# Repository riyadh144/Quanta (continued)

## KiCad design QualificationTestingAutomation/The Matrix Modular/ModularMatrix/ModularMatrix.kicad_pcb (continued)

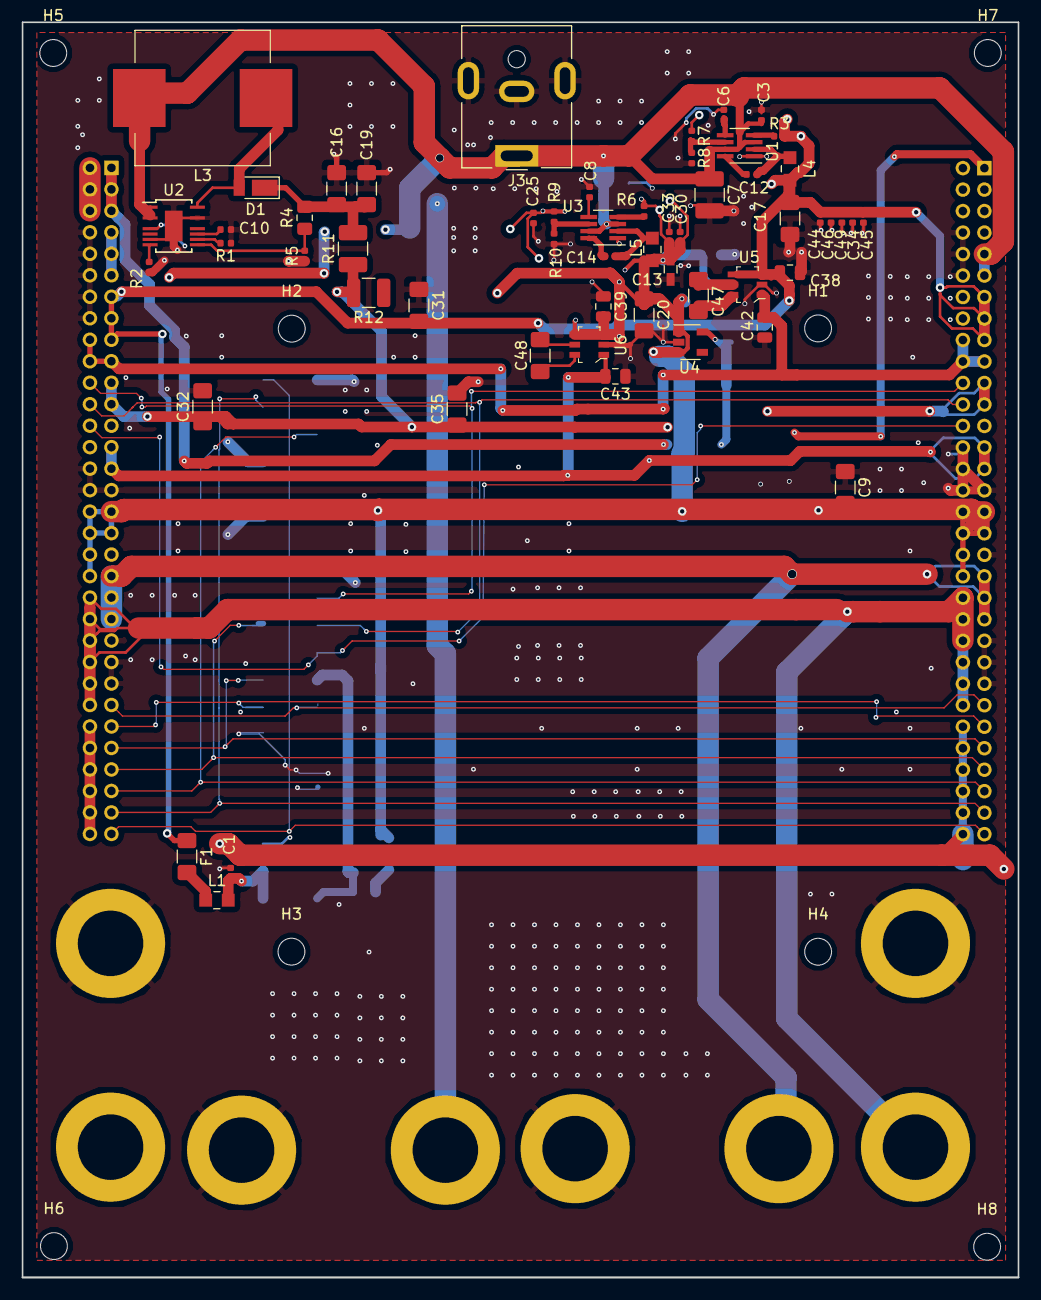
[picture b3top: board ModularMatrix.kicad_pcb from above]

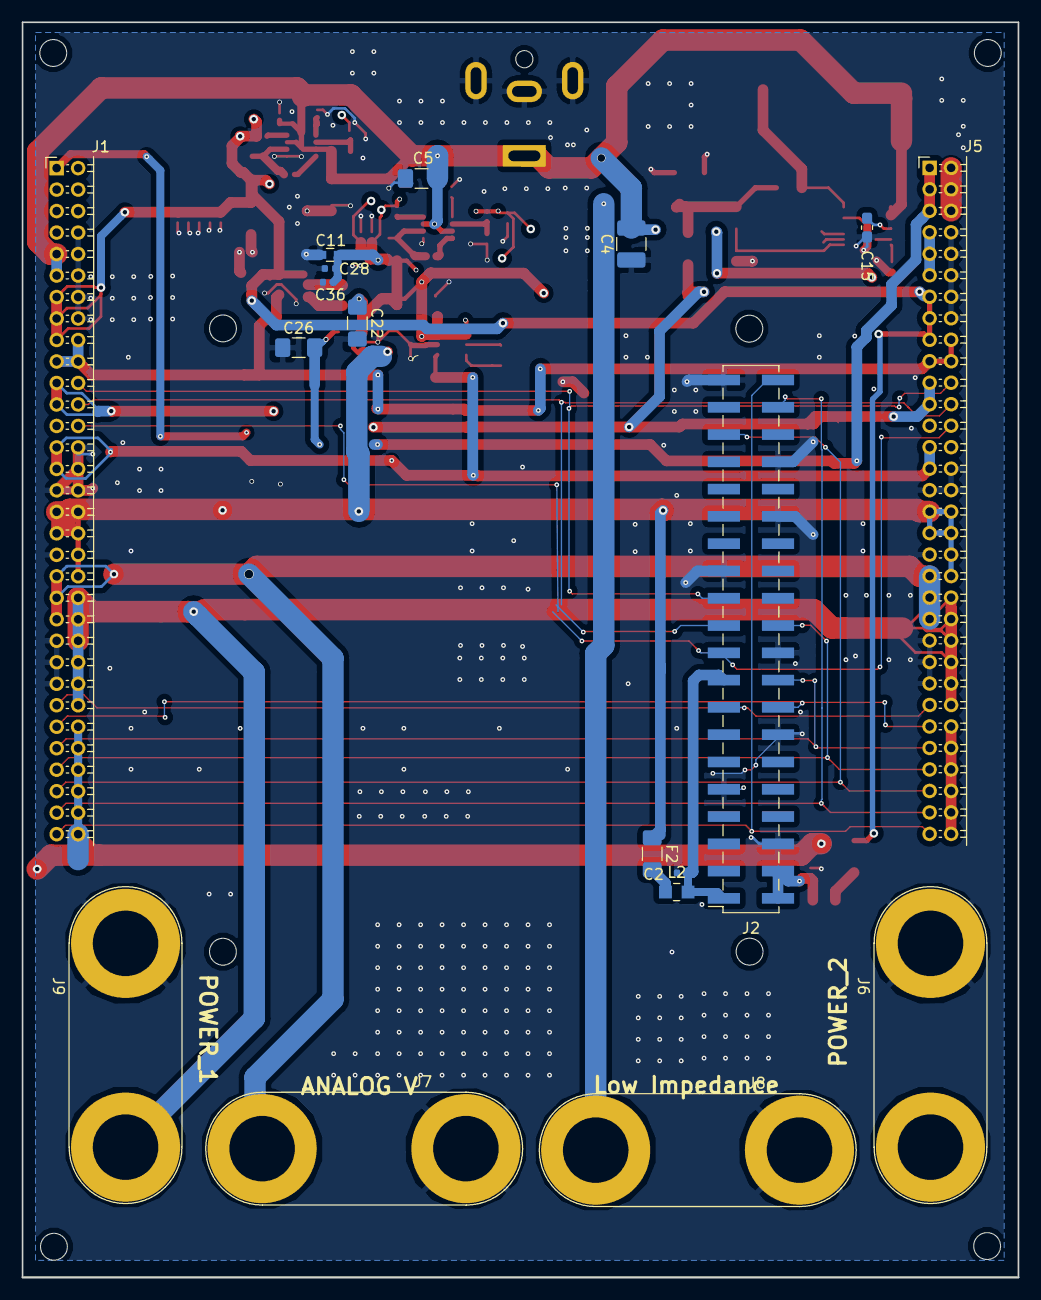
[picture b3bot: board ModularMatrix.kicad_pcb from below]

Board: 4 copper layers, 92.7 x 116.8 mm, 82 parts (18 on the bottom side), 47 nets.

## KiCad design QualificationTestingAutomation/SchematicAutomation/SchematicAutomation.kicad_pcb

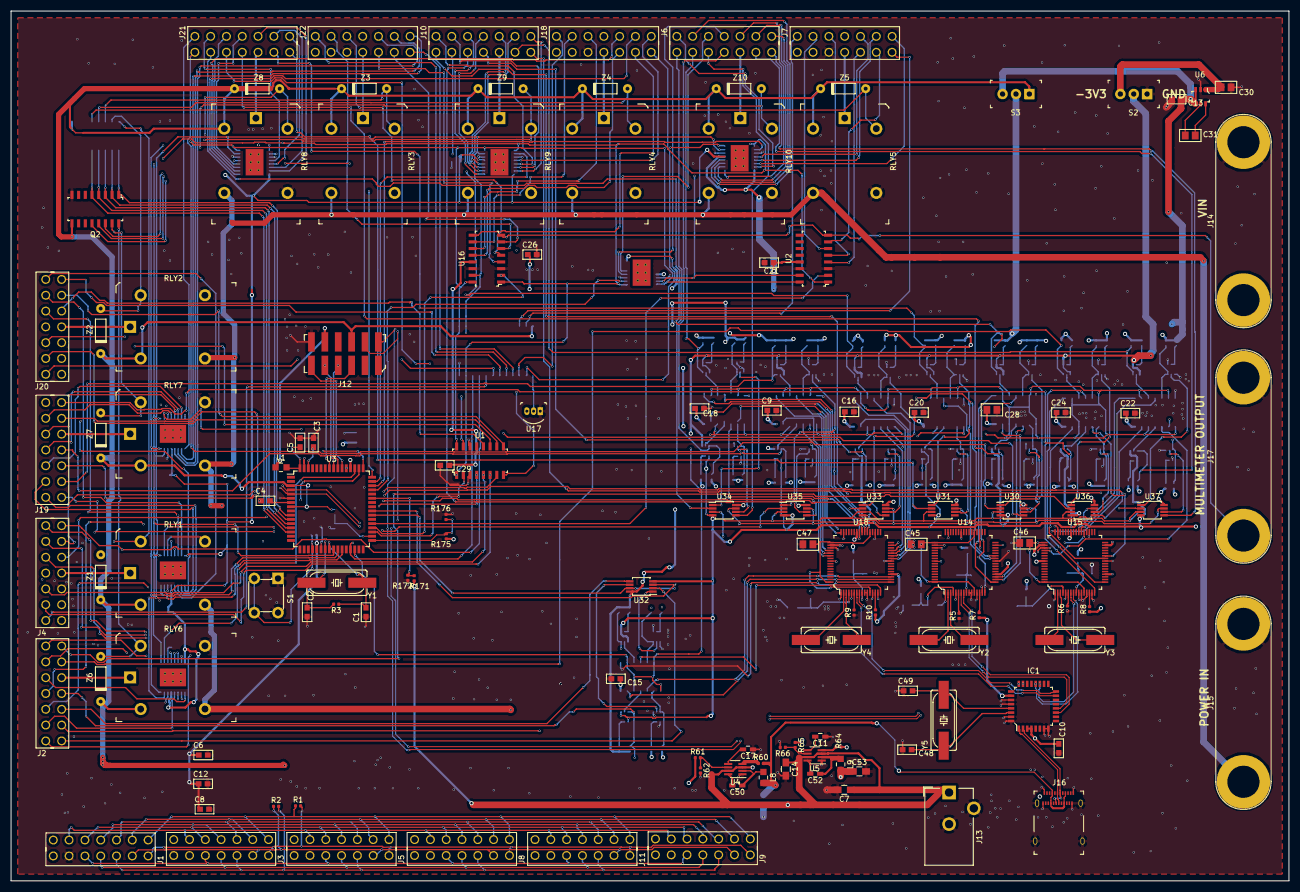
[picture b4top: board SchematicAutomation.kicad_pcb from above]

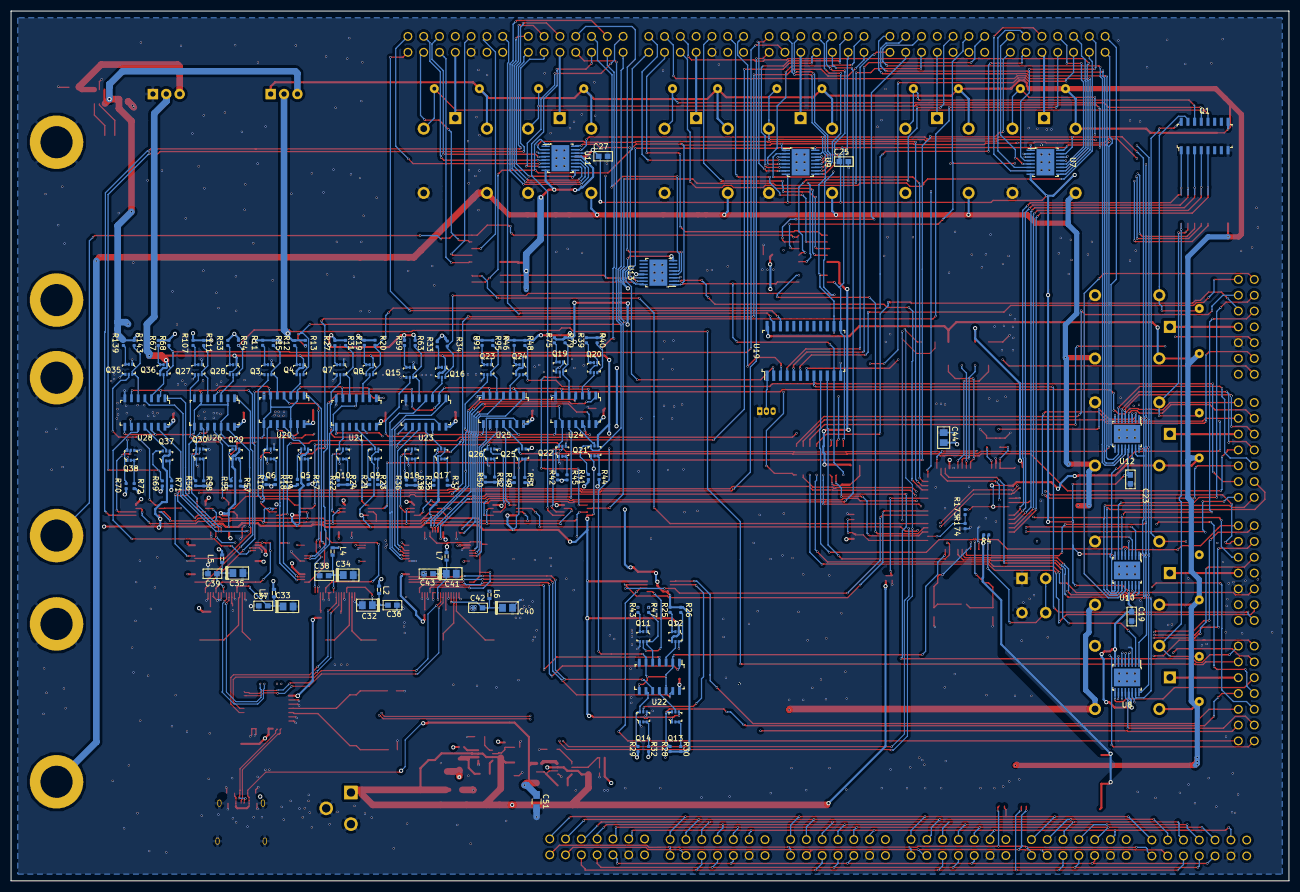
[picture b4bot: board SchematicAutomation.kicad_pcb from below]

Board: 4 copper layers, 242.6 x 165.1 mm, 268 parts (140 on the bottom side), 343 nets.

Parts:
C1, C2, C48, C49: 20pF; C-0603
C3, C5, C36, C37, C38, C39, C42, C43: 100nF; C-0603
C4: 1uF; C-0603
C6, C8, C9, C10, C12, C13, C15, C16, C18, C19, C20, C21, C22, C23, C24, C25, C26, C27, C29: .01uF; C-0603
C7, C14: 22uF; C_0805_HandSoldering
C11, C17: 8.2nF; C_0603_HandSoldering
C28, C30: 2.2uF; C-0805
C31: 1uF; C-0805
C32, C33, C34, C35, C40, C41: 4.7uF; CPL-0805
C44: 4.7uF; C-0805
C45, C46, C47: 3.3uF; C-0805
C50, C52: 100nF; C_0603_HandSoldering
C51, C53: 47uF; C_0805_HandSoldering
IC1: TUSB2046B; LQFP-32_7x7mm
J1, J2, J3, J4, J5, J6, J7, J8, J9, J10, J11, J18, J19, J20, J21, J22: OBD Connector; 3MM
J12: 0015912120; PinHeader_2x6_P2.54mm_Vertical_SMD
J13: Barrel_Jack_MountingPin; Barrel_Jack_CUI_PJ-102AH
J14, J15, J17: Banana Jack; Banana_Jack_2Pin
J16: 12401610E4_2A; USB_Type_C_Female__12401610E4_2A
L1: 10uH; 0805
L2, L3, L4, L5, L6, L7: L_Core_Ferrite; 0603
L8, L9: 3.3uH; 0805
Q1, Q2: ULN2003ADR; SOIC-16_W3.90mm
Q3, Q4, Q5, Q6, Q7, Q8, Q9, Q10, Q11, Q12, Q13, Q14, Q15, Q16, Q17, Q18, Q19, Q20, Q21, Q22, Q23, Q24, Q25, Q26, Q27, Q28, Q29, Q30, Q35, Q36, Q37, Q38: 2N7002DW; SOT-363
R1, R2: R120; R_0402_1005Metric
R3: 1M; R_0402_1005Metric
R4, R60, R64, R171, R173, R175, R176: 100K; R_0402_1005Metric
R5, R6, R9: 12K; R_0402_1005Metric
R7, R8, R10: 1K; R_0402_1005Metric
R11, R12, R13, R14, R15, R16, R17, R18, R19, R20, R21, R22, R23, R24, R25, R26, R27, R28, R29, R30, R31, R32, R33, R34, R35, R36, R37, R38, R39, R40, R41, R42, R43, R44, R45, R46, R47, R48, R49, R50, R51, R52, R53, R54, R55, R56, R57, R58, R59, R63, R67, R68, R69, R70, R71, R72, R75, R79, R91, R95, R107, R111, R139, R143: 10k; R_0402_1005Metric
R61: 56.2K; R_0402_1005Metric
R62, R66, R172: 10K; R_0402_1005Metric
R65: 33.2K; R_0402_1005Metric
R174: 50K; R_0402_1005Metric
RLY1, RLY2, RLY3, RLY4, RLY5, RLY6, RLY7, RLY8, RLY9, RLY10: G5LE-14_DC5; Relay_THT_G5LE-14
S1: 1825910-6; Switch_Tactile_THT_6x6mm
S2, S3: ATE1D-2M3-10-Z; Switch_Toggle_ATE1D-2M3-10-Z
U1, U2, U16: DG408LE; SOIC-16_W3.90mm
U3: AT90USB1287-AU; TQFP-64_14x14mm_P0.8mm
U4, U5: TPS563210; SOT-23-8_Handsoldering
U6: LM2776; SOT-23-6
U7, U8, U9, U10, U11, U12, U13: MAX14752; TSSOP-16-1EP_W4.40mm
U14, U15, U18: FT4232HL-REEL; LQFP-64_10x10mm
U17: DS18B20_; TO-92-3
U19: CD74HC4067SM96; SSOP-24_W5.30mm
U20, U21, U22, U23, U24, U25, U26, U28: CD4070B; SOIC-14_W3.9mm
U30, U31, U32, U33, U34, U35, U36, U37: MAX324CUA; MSOP-8_3x3mm_Pitch0.65mm
Y1: 16MHz; HC49UP
Y2, Y3, Y4: 12MHz; HC49UP
Y5: 6MHz; HC49UP
Z1, Z2, Z3, Z4, Z5, Z6, Z7, Z8, Z9, Z10: 1N5231BTR; DO-35

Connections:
1_ADC0: J4.10, U8.4
1_ADC1: J2.14, U8.7
1_ADC2: J4.8, U8.6
1_ADC3: J4.9, U8.5
1_CANHigh: J1.1, J3.1, J5.1, J8.1, J9.1, J11.1, R1.1
1_CANLow: J1.14, J3.14, J5.14, J8.14, J9.14, J11.14, R1.2
1_CAN_MS_H: J1.13, J3.13, J5.13, J8.13, J9.13, J11.13, R2.1
1_CAN_MS_L: J1.12, J3.12, J5.12, J8.12, J9.12, J11.12, R2.2
1_CTS: J2.3, U32.5
1_GarminPWR: J2.5, RLY6.1
1_GarminRX: J2.6, Q28.6, R54.1
1_GarminTX: J2.7, U36.2
1_IN0: J2.13, U8.12
1_IN1: J2.8, U8.11
1_IN2: J2.9, U8.10
1_IN3: J2.10, U8.9
1_IN4: J2.11, U10.4
1_IN5: J2.12, U10.5
1_ISO-K: J1.10, J3.10, J5.10, J8.10, J9.10, J11.10
1_ISO-Low: J1.4, J3.4, J5.4, J8.4, J9.4, J11.4
1_J1708-RXD: J1.2, J3.2, J5.2, J8.2, J9.2, J11.2
1_J1708-TXD: J1.3, J3.3, J5.3, J8.3, J9.3, J11.3
1_J1850+: J1.6, J3.6, J5.6, J8.6, J9.6, J11.6
1_J1850-: J1.5, J3.5, J5.5, J8.5, J9.5, J11.5
1_OUT0: J4.5, U1.4
1_OUT1: J4.12, U1.5
1_OUT2: J4.13, U1.6
1_OUT3: J4.6, U1.7
1_OWB_MAIN: J4.14, U19.8
1_OWB_SEC: J4.7, U19.9
1_REL: Q1.1, Q2.1, U3.10
1_RTS: J2.4, Q13.6, R28.1
1_RX: J2.2, Q12.6, R26.1
1_SWC_BUS: J1.11, J3.11, J5.11, J8.11, J9.11, J11.11
1_TX: J2.1, U32.2
1_Vin: J4.4, RLY1.1
2_ADC0: J20.10, U10.6
2_ADC1: J19.14, U10.11
2_ADC2: J20.8, U10.12
2_ADC3: J20.9, U10.7
2_CTS: J19.3, U35.5
2_GarminPWR: J19.5, RLY7.1
2_GarminRX: J19.6, U36.5
2_GarminTX: J19.7, Q29.6, R55.1
2_IN0: J19.13, U10.10
2_IN1: J19.8, U10.9
2_IN2: J19.9, U12.4
2_IN3: J19.10, U12.5
2_IN4: J19.11, U12.6
2_IN5: J19.12, U12.7
2_OUT0: J20.5, U1.12
2_OUT1: J20.12, U1.11
2_OUT2: J20.13, U1.10
2_OUT3: J20.6, U1.9
2_OWB_MAIN: J20.14, U19.7
2_OWB_SEC: J20.7, U19.6
2_REL: Q1.2, Q2.2, U3.11
2_RTS: J19.4, Q25.6, R49.1
2_RX: J19.2, Q24.6, R48.1
2_TX: J19.1, U35.2
2_Vin: J20.4, RLY2.1
3_ADC0: J22.10, U12.12
3_ADC1: J21.14, U12.9
3_ADC2: J22.8, U12.10
3_ADC3: J22.9, U12.11
3_CTS: J21.3, U30.5
3_GarminPWR: J21.5, RLY8.1
3_GarminRX: J21.6, Q8.6, R20.1
3_GarminTX: J21.7, U31.2
3_IN0: J21.13, U7.4
3_IN1: J21.8, U7.5
3_IN2: J21.9, U7.6
3_IN3: J21.10, U7.7
3_IN4: J21.11, U7.12
3_IN5: J21.12, U7.11
3_OUT0: J22.5, U16.4
3_OUT1: J22.12, U16.5
3_OUT2: J22.13, U16.6
3_OUT3: J22.6, U16.7
3_OWB_MAIN: J22.14, U19.5
3_OWB_SEC: J22.7, U19.4
3_REL: Q1.3, Q2.3, U3.12
3_RTS: J21.4, Q5.6, R14.1
3_RX: J21.2, Q4.6, R13.1
3_TX: J21.1, U30.2
3_Vin: J22.4, RLY3.1
4_ADC0: J18.10, U7.10
4_ADC1: J10.14, U9.5
4_ADC2: J18.8, U9.4
4_ADC3: J18.9, U7.9
4_CTS: J10.3, U33.5
4_GarminPWR: J10.5, RLY9.1
4_GarminRX: J10.6, Q36.6, R68.1
4_GarminTX: J10.7, U37.2
4_IN0: J10.13, U9.6
4_IN1: J10.8, U9.7
4_IN2: J10.9, U9.12
4_IN3: J10.10, U9.11
4_IN4: J10.11, U9.10
4_IN5: J10.12, U9.9
4_OUT0: J18.5, U16.12
4_OUT1: J18.12, U16.11
4_OUT2: J18.13, U16.10
4_OUT3: J18.6, U16.9
4_OWB_MAIN: J18.14, U19.3
4_OWB_SEC: J18.7, U19.2
4_REL: Q1.4, Q2.4, U3.13
4_RTS: J10.4, Q17.6, R35.1
4_RX: J10.2, Q16.6, R34.1
4_TX: J10.1, U33.2
4_Vin: J18.4, RLY4.1
5_ADC0: J7.10, U11.4
5_ADC1: J6.14, U11.7
5_ADC2: J7.8, U11.6
5_ADC3: J7.9, U11.5
5_CTS: J6.3, U34.5
5_GarminPWR: J6.5, RLY10.1
5_GarminRX: J6.6, Q37.6, R69.1
5_GarminTX: J6.7, U37.5
5_IN0: J6.13, U11.12
5_IN1: J6.8, U11.11
5_IN2: J6.9, U11.10
5_IN3: J6.10, U11.9
5_IN4: J6.11, U13.4
5_IN5: J6.12, U13.5
5_OUT0: J7.5, U2.4
5_OUT1: J7.12, U2.5
5_OUT2: J7.13, U2.6
5_OUT3: J7.6, U2.7
5_OWB_MAIN: J7.14, U19.23
5_OWB_SEC: J7.7, U19.22
5_REL: Q1.5, Q2.5, U3.14
5_RTS: J6.4, Q21.6, R41.1
5_RX: J6.2, Q20.6, R40.1
5_TX: J6.1, U34.2
5_Vin: J7.4, RLY5.1
+3V3: C6.1, C8.1, C9.1, C10.1, C12.1, C13.1, C15.1, C16.1, C18.1, C20.1, C22.1, C24.1, C28.2, C44.2, C53.1, IC1.3, IC1.4, IC1.26, J12.11, L1.1, L2.2, L3.2, L4.2, L5.2, L6.2, L7.2, L9.2, R4.2, R7.1, R8.1, R10.1, R11.1, R15.2, R16.2, R18.1, R22.2, R24.1, R27.1, R29.2, R31.2, R32.1, R36.2, R38.1, R42.2, R43.1, R45.1, R47.2, R50.2, R52.1, R56.2, R58.1, R59.1, R63.2, R64.2, R65.1, R70.2, R72.1, R75.1, R79.2, R91.1, R95.2, R107.1, R111.2, R139.1, R143.2, R175.1, S3.3, U3.21, U3.52, U6.3, U6.4, U14.20, U14.31, U14.42, U14.50, U14.56, U15.20, U15.31, U15.42, U15.50, U15.56, U18.20, U18.31, U18.42, U18.50, U18.56, U20.14, U21.14, U22.14, U23.14, U24.14, U25.14, U26.14, U28.14
+5V: C51.1, J12.9, J16.A4, J16.A9, J16.B4, J16.B9, L8.2, Q1.9, Q2.9, R60.2, R61.1, R173.1, RLY1.2, RLY2.2, RLY3.2, RLY4.2, RLY5.2, RLY6.2, RLY7.2, RLY8.2, RLY9.2, RLY10.2, S3.1, U3.3, U3.8, U19.24, Z1.K, Z2.K, Z3.K, Z4.K, Z5.K, Z6.K, Z7.K, Z8.K, Z9.K, Z10.K
+12V: C7.1, C14.1, J13.1, R171.1, U4.3, U4.7, U5.3, U5.7
+VSW: R12.1, R13.2, R14.2, R17.1, R19.1, R20.2, R21.2, R23.1, R25.1, R26.2, R28.2, R30.1, R33.1, R34.2, R35.2, R37.1, R39.1, R40.2, R41.2, R44.1, R46.1, R48.2, R49.2, R51.1, R53.1, R54.2, R55.2, R57.1, R67.1, R68.2, R69.2, R71.1, S3.2, U30.8, U31.8, U32.8, U33.8, U34.8, U35.8, U36.8, U37.8
-3V3: C30.2, S2.3, U6.1
-VSW: Q4.1, Q4.4, Q5.1, Q5.4, Q8.1, Q8.4, Q9.1, Q9.4, Q12.1, Q12.4, Q13.1, Q13.4, Q16.1, Q16.4, Q17.1, Q17.4, Q20.1, Q20.4, Q21.1, Q21.4, Q24.1, Q24.4, Q25.1, Q25.4, Q28.1, Q28.4, Q29.1, Q29.4, Q36.1, Q36.4, Q37.1, Q37.4, S2.2, U30.4, U31.4, U32.4, U33.4, U34.4, U35.4, U36.4, U37.4
/ATMEGA2560/D+: IC1.24, J12.7, U3.5
/ATMEGA2560/D-: IC1.23, J12.8, U3.4
/ATMEGA2560/TCK: J12.3, U3.57
/ATMEGA2560/TDI: J12.6, U3.54
/ATMEGA2560/TDO: J12.5, U3.55
/ATMEGA2560/TMS: J12.4, U3.56
/D1+: IC1.11, U14.8
/D1-: IC1.12, U14.7
/D2+: IC1.16, U18.8
/D2-: IC1.15, U18.7
/D3+: IC1.20, U15.8
/D3-: IC1.19, U15.7
/RS232/sheet5BB9E804/CTS_3V3: U14.19, U20.10
/RS232/sheet5BB9E804/RTS_3V3: U14.18, U20.13
/RS232/sheet5BB9E804/RX_3V3: U14.17, U20.1
/RS232/sheet5BB9E804/Tx_3V3: U14.16, U20.4
/RS232/sheet5BBDE283/RTS: Q9.6, R21.1
/RS232/sheet5BBDE283/RX_3V3: U14.27, U21.1
/RS232/sheet5BBDE283/Tx_3V3: U14.26, U21.4
/RS232/sheet5BC0E596/CTS_3V3: U18.29, U23.10
/RS232/sheet5BC0E596/RTS_3V3: U18.28, U23.13
/RS232/sheet5BC0E596/RX_3V3: U18.27, U23.1
/RS232/sheet5BC0E596/Tx_3V3: U18.26, U23.4
/RS232/sheet5BC04BA5/CTS_3V3: U18.19, U22.10
/RS232/sheet5BC04BA5/RTS_3V3: U18.18, U22.13
/RS232/sheet5BC04BA5/RX_3V3: U18.17, U22.1
/RS232/sheet5BC04BA5/Tx_3V3: U18.16, U22.4
/RS232/sheet5BC17F87/CTS_3V3: U18.41, U24.10
/RS232/sheet5BC17F87/RTS_3V3: U18.40, U24.13
/RS232/sheet5BC17F87/RX_3V3: U18.39, U24.1
/RS232/sheet5BC17F87/Tx_3V3: U18.38, U24.4
/RS232/sheet5BC21962/CTS_3V3: U18.54, U25.10
/RS232/sheet5BC21962/RTS_3V3: U18.53, U25.13
/RS232/sheet5BC21962/RX_3V3: U18.52, U25.1
/RS232/sheet5BC21962/Tx_3V3: U18.48, U25.4
/RS232/sheet5BD54784/CTS_3V3: U15.27, U26.10
/RS232/sheet5BD54784/RTS_3V3: U15.26, U26.13
/RS232/sheet5BD54784/RX_3V3: U15.17, U26.1
/RS232/sheet5BD54784/Tx_3V3: U15.16, U26.4
/RS232/sheet5BDC5154/CTS_3V3: U15.52, U28.10
/RS232/sheet5BDC5154/RTS_3V3: U15.48, U28.13
/RS232/sheet5BDC5154/RX_3V3: U15.39, U28.1
/RS232/sheet5BDC5154/Tx_3V3: U15.38, U28.4
/USBInterface/D0+: IC1.1, J16.A6, J16.B6
/USBInterface/D0-: IC1.2, J16.A7, J16.B7
CTS_CONT: U3.40, U30.3, U31.3, U32.3, U33.3, U34.3, U35.3, U36.3, U37.3
GND: C1.1, C2.2, C3.1, C4.1, C5.2, C6.2, C7.2, C8.2, C9.2, C10.2, C11.1, C12.2, C13.2, C14.2, C15.2, C16.2, C17.1, C18.2, C19.2, C20.2, C21.2, C22.2, C23.2, C24.2, C25.2, C26.2, C27.2, C28.1, C29.2, C30.1, C32.K, C33.K, C34.K, C35.K, C36.1, C37.1, C38.1, C39.1, C40.K, C41.K, C42.1, C43.1, C44.1, C45.1, C46.1, C47.1, C48.2, C49.1, C51.2, C53.2, IC1.7, IC1.8, IC1.27, IC1.28, IC1.31, IC1.32, J1.9, J3.9, J4.3, J5.9, J7.3, J8.9, J9.9, J11.9, J12.12, J13.2, J13.3, J14.2, J15.2, J16.A1, J16.A12, J16.B1, J16.B12, J16.SH, J17.2, J18.3, J20.3, J22.3, Q1.8, Q2.8, Q3.1, Q3.4, Q6.1, Q6.4, Q7.1, Q7.4, Q10.1, Q10.4, Q11.1, Q11.4, Q14.1, Q14.4, Q15.1, Q15.4, Q18.1, Q18.4, Q19.1, Q19.4, Q22.1, Q22.4, Q23.1, Q23.4, Q26.1, Q26.4, Q27.1, Q27.4, Q30.1, Q30.4, Q35.1, Q35.4, Q38.1, Q38.4, R5.1, R6.1, R9.1, R62.2, R66.2, R172.2, R174.2, R176.2, RLY1.4, RLY2.4, RLY3.4, RLY4.4, RLY5.4, RLY6.4, RLY7.4, RLY8.4, RLY9.4, RLY10.4, S1.1, S1.2, S2.1, U1.3, U1.14, U2.3, U2.14, U3.6, U3.22, U3.53, U3.63, U4.1, U5.1, U6.2, U7.3, U7.14, U8.3, U8.14, U9.3, U9.14, U10.3, U10.14, U11.3, U11.14, U12.3, U12.14, U13.3, U13.14, U14.1, U14.5, U14.10, U14.11, U14.13, U14.15, U14.25, U14.35, U14.47, U14.51, U15.1, U15.5, U15.10, U15.11, U15.13, U15.15, U15.25, U15.35, U15.47, U15.51, U16.3, U16.14, U17.1, U18.1, U18.5, U18.10, U18.11, U18.13, U18.15, U18.25, U18.35, U18.47, U18.51, U19.12, U20.7, U21.7, U22.7, U23.7, U24.7, U25.7, U26.7, U28.7
MUX16: U3.48, U7.2
MUX17: U3.51, U8.2
MUX18: U3.47, U9.2
MUX19: U3.50, U10.2
MUX20: U3.46, U11.2
MUX21: U3.49, U12.2
MUX22: U3.45, U13.2
MUX24: U2.2, U3.37
MUX25: U3.36, U16.2
MUX26: U1.2, U3.35
MUXA1: U3.29, U19.10
MUXC: U1.1, U2.1, U3.25, U7.1, U8.1, U9.1, U10.1, U11.1, U12.1, U13.1, U16.1, U19.11
MUXD: U1.16, U2.16, U3.26, U7.16, U8.16, U9.16, U10.16, U11.16, U12.16, U13.16, U16.16, U19.13
MUXE: U1.15, U2.15, U3.27, U7.15, U8.15, U9.15, U10.15, U11.15, U12.15, U13.15, U16.15, U19.14
unnamed: C1.2, R3.1, U3.24, Y1.1
unnamed: C2.1, R3.2, U3.23, Y1.2
unnamed: C3.2, U3.62
unnamed: C4.2, U3.7
unnamed: C5.1, L1.2, U3.64
unnamed: C11.2, U5.5
unnamed: C17.2, U4.5
unnamed: C31.1, U6.5
unnamed: C31.2, U6.6
unnamed: C32.A, C36.2, L2.1, U14.4
unnamed: C33.A, C37.2, L3.1, U15.4
unnamed: C34.A, C38.2, L4.1, U14.9
unnamed: C35.A, C39.2, L5.1, U15.9
unnamed: C40.A, C42.2, L6.1, U18.4
unnamed: C41.A, C43.2, L7.1, U18.9
unnamed: C45.2, U14.12, U14.37, U14.49, U14.64
unnamed: C46.2, U15.12, U15.37, U15.49, U15.64
unnamed: C47.2, U18.12, U18.37, U18.49, U18.64
unnamed: C48.1, IC1.30, Y5.1
unnamed: C49.2, IC1.29, Y5.2
unnamed: C50.1, L8.1, U4.2
unnamed: C50.2, U4.8
unnamed: C52.1, L9.1, U5.2
unnamed: C52.2, U5.8
unnamed: J17.1, U1.8, U2.8, U16.8
unnamed: Q1.12, RLY5.5, Z5.A
unnamed: Q1.13, RLY4.5, Z4.A
unnamed: Q1.14, RLY3.5, Z3.A
unnamed: Q1.15, RLY2.5, Z2.A
unnamed: Q1.16, RLY1.5, Z1.A
unnamed: Q2.12, RLY10.5, Z10.A
unnamed: Q2.13, RLY9.5, Z9.A
unnamed: Q2.14, RLY8.5, Z8.A
unnamed: Q2.15, RLY7.5, Z7.A
unnamed: Q2.16, RLY6.5, Z6.A
unnamed: Q3.2, Q3.3, R11.2
unnamed: Q3.5, U30.1
unnamed: Q3.6, R15.1, U20.5
unnamed: Q4.2, Q4.3, R12.2
unnamed: Q4.5, U20.3
unnamed: Q5.2, Q5.3, R17.2
unnamed: Q5.5, U20.11
unnamed: Q6.2, Q6.3, R18.2
unnamed: Q6.5, U30.6
unnamed: Q6.6, R16.1, U20.9
unnamed: Q7.2, Q7.3, R27.2
unnamed: Q7.5, U31.1
unnamed: Q7.6, R31.1, U21.5
unnamed: Q8.2, Q8.3, R19.2
unnamed: Q8.5, U21.3
unnamed: Q9.2, Q9.3, R23.2
unnamed: Q9.5, U21.11
unnamed: Q10.2, Q10.3, R24.2
unnamed: Q10.5, U31.6
unnamed: Q10.6, R22.1, U21.9
unnamed: Q11.2, Q11.3, R43.2
unnamed: Q11.5, U32.1
unnamed: Q11.6, R47.1, U22.5
unnamed: Q12.2, Q12.3, R25.2
unnamed: Q12.5, U22.3
unnamed: Q13.2, Q13.3, R30.2
unnamed: Q13.5, U22.11
unnamed: Q14.2, Q14.3, R32.2
unnamed: Q14.5, U32.6
unnamed: Q14.6, R29.1, U22.9
unnamed: Q15.2, Q15.3, R59.2
unnamed: Q15.5, U33.1
unnamed: Q15.6, R63.1, U23.5
unnamed: Q16.2, Q16.3, R33.2
unnamed: Q16.5, U23.3
unnamed: Q17.2, Q17.3, R37.2
unnamed: Q17.5, U23.11
unnamed: Q18.2, Q18.3, R38.2
unnamed: Q18.5, U33.6
unnamed: Q18.6, R36.1, U23.9
unnamed: Q19.2, Q19.3, R75.2
unnamed: Q19.5, U34.1
unnamed: Q19.6, R79.1, U24.5
unnamed: Q20.2, Q20.3, R39.2
unnamed: Q20.5, U24.3
unnamed: Q21.2, Q21.3, R44.2
unnamed: Q21.5, U24.11
unnamed: Q22.2, Q22.3, R45.2
unnamed: Q22.5, U34.6
unnamed: Q22.6, R42.1, U24.9
unnamed: Q23.2, Q23.3, R91.2
unnamed: Q23.5, U35.1
unnamed: Q23.6, R95.1, U25.5
unnamed: Q24.2, Q24.3, R46.2
unnamed: Q24.5, U25.3
unnamed: Q25.2, Q25.3, R51.2
unnamed: Q25.5, U25.11
unnamed: Q26.2, Q26.3, R52.2
unnamed: Q26.5, U35.6
unnamed: Q26.6, R50.1, U25.9
unnamed: Q27.2, Q27.3, R107.2
unnamed: Q27.5, U36.1
unnamed: Q27.6, R111.1, U26.5
unnamed: Q28.2, Q28.3, R53.2
unnamed: Q28.5, U26.3
unnamed: Q29.2, Q29.3, R57.2
unnamed: Q29.5, U26.11
unnamed: Q30.2, Q30.3, R58.2
unnamed: Q30.5, U36.6
unnamed: Q30.6, R56.1, U26.9
unnamed: Q35.2, Q35.3, R139.2
unnamed: Q35.5, U37.1
unnamed: Q35.6, R143.1, U28.5
unnamed: Q36.2, Q36.3, R67.2
unnamed: Q36.5, U28.3
unnamed: Q37.2, Q37.3, R71.2
unnamed: Q37.5, U28.11
unnamed: Q38.2, Q38.3, R72.2
unnamed: Q38.5, U37.6
unnamed: Q38.6, R70.1, U28.9
unnamed: R4.1, S1.3, S1.4, U3.20
unnamed: R5.2, U14.6
unnamed: R6.2, U15.6
unnamed: R7.2, U14.14
unnamed: R8.2, U15.14
unnamed: R9.2, U18.6
unnamed: R10.2, U18.14
unnamed: R60.1, U4.4
unnamed: R61.2, R62.1, U4.6
unnamed: R64.1, U5.4
unnamed: R65.2, R66.1, U5.6
unnamed: R171.2, R172.1, U3.43
unnamed: R173.2, R174.1, U3.34
unnamed: R175.2, R176.1, U3.33
unnamed: U14.2, Y2.2
unnamed: U14.3, Y2.1
unnamed: U15.2, Y3.2
unnamed: U15.3, Y3.1
unnamed: U17.2, U19.1
unnamed: U18.2, Y4.2
unnamed: U18.3, Y4.1
RS232INV: U3.30, U20.2, U20.6, U20.8, U20.12, U21.2, U21.6, U21.8, U21.12, U22.2, U22.6, U22.8, U22.12, U23.2, U23.6, U23.8, U23.12, U24.2, U24.6, U24.8, U24.12, U25.2, U25.6, U25.8, U25.12, U26.2, U26.6, U26.8, U26.12, U28.2, U28.6, U28.8, U28.12
TX_CONT: U3.39, U30.7, U31.7, U32.7, U33.7, U34.7, U35.7, U36.7, U37.7
VAA: C19.1, C21.1, C23.1, C25.1, C26.1, C27.1, C29.1, J14.1, U1.13, U2.13, U7.8, U7.13, U8.8, U8.13, U9.8, U9.13, U10.8, U10.13, U11.8, U11.13, U12.8, U12.13, U13.8, U13.13, U16.13
VDC: J15.1, RLY1.3, RLY2.3, RLY3.3, RLY4.3, RLY5.3, RLY6.3, RLY7.3, RLY8.3, RLY9.3, RLY10.3

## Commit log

2018-08-29 modified: Main.java
2018-09-03 new file: Symbols/Analog Multiplexers/MAX14756EUET/MAX14756EUET.dcm new file: Symbols/Analog Multiplexers/MAX14756EUET/MAX14756EUET.lib new file: Symbols/Analog Multiplexers/MAX14756EUET/MAX14756EUET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
2018-09-03 new file: QualificationTestingAutomation/SchematicAutomation/IO.bak new file: QualificationTestingAutomation/SchematicAutomation/IO.sch new file: QualificationTestingAutomation/SchematicAutomation/MS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
2018-09-04 modified: NMEAGUI/.classpath modified: NMEAGUI/.settings/org.eclipse.jdt.core.prefs new file: NMEAGUI/src/.classpath new file: NMEAGUI/src/.project new file: NMEAGUI/src/application/.gitignore modifi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
2018-09-06 schematic is finished a few symbols were added, footprints are almost done, some work needs to be done on the connectors#
2018-09-08 C WPCB was started and the schematic is full, I am thinking of implementing the UART test using analog muxes.
2018-09-10 the PCB is complete and has been ordered
2018-09-11 Cleaned up the PCB removed the vias from the pads.
2018-09-11 added schematic symbols
2018-09-12 Started the coding and some clean up of the pcb
2018-09-15 Adding a google verification file
2018-10-05 Added Schematic Libraries
2018-10-05 CLEANED UP THE SCHEMATICS ADDED NEADED FIXES FOUND ON THE BOARD
2018-10-05 Basis for the software
2018-10-08 Revert "Basis for the software"
    This reverts commit 86387e2806cd51dba67378f63d3994c3c554d8f8.
    # Conflicts:
    # QualificationTestingAutomation/SchematicAutomation/Library Schematic/SchematicAutomation-cache.lib
    # QualificationTestingAutomation/SchematicAutomation/USB.bak
    # QualificationTestingAutomation/SchematicAutomation/USB.sch
2018-10-08 USB test instrument support and SCPI support were added to the FW
2018-10-08 RX TX mixup was solved by changing RX_3V3 and TX_3V3 on the XOR side Same goes for CTS and RTS and some general clean up
2019-03-13 Changed Schematic Names Added Raspberry Pi support to the board
2019-03-13 Raspberry Pi Support Changed the name of the Project
2019-03-14 Added 60V supply for the MUX's so they can be independent from Vpower, Added another seperate power rail
2019-03-14 Some Track cleanups
2019-03-27 Major upgrade, Finished laying out switcheroo, and the Matrix.
2019-03-27 Cleaned up the libraries Cleaned up the tracks Adjusted footprints to the manufacturers minimum size.
2019-03-28 Added Voltage and current measurment of the muxes and relays to the MSP Some clean up of the tracks.
2019-03-28 Updated the layout to accomodate the voltage and current sensing.
2019-03-31 Schematic Clean ups the layout needs to be changed
2019-04-03 IO clean up added the 1v25 reference to Matrix Changed Some of the labels to more legible names.
2019-05-01 Reefero Module PCB design
